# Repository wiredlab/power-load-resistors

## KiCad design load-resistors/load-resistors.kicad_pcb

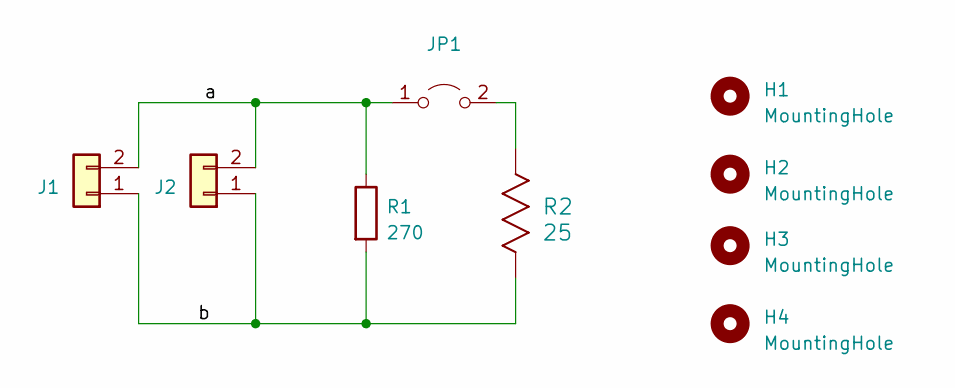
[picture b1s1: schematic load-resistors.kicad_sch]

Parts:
H1, H2, H3, H4: MountingHole; MountingHole_3.2mm_M3
J1, J2: Conn_01x02; Molex_KK-254_AE-6410-02A_1x02_P2.54mm_Vertical
JP1: Jumper_2_Open; PinHeader_1x02_P2.54mm_Vertical
R1: 270; R_Axial_Power_L25.0mm_W9.0mm_P30.48mm
R2: 25; KAL25FB25R0

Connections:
/a: J1.2, J2.2, JP1.1 (A), R1.1
/b: J1.1, J2.1, R1.2, R2.1
unnamed: JP1.2 (B), R2.2

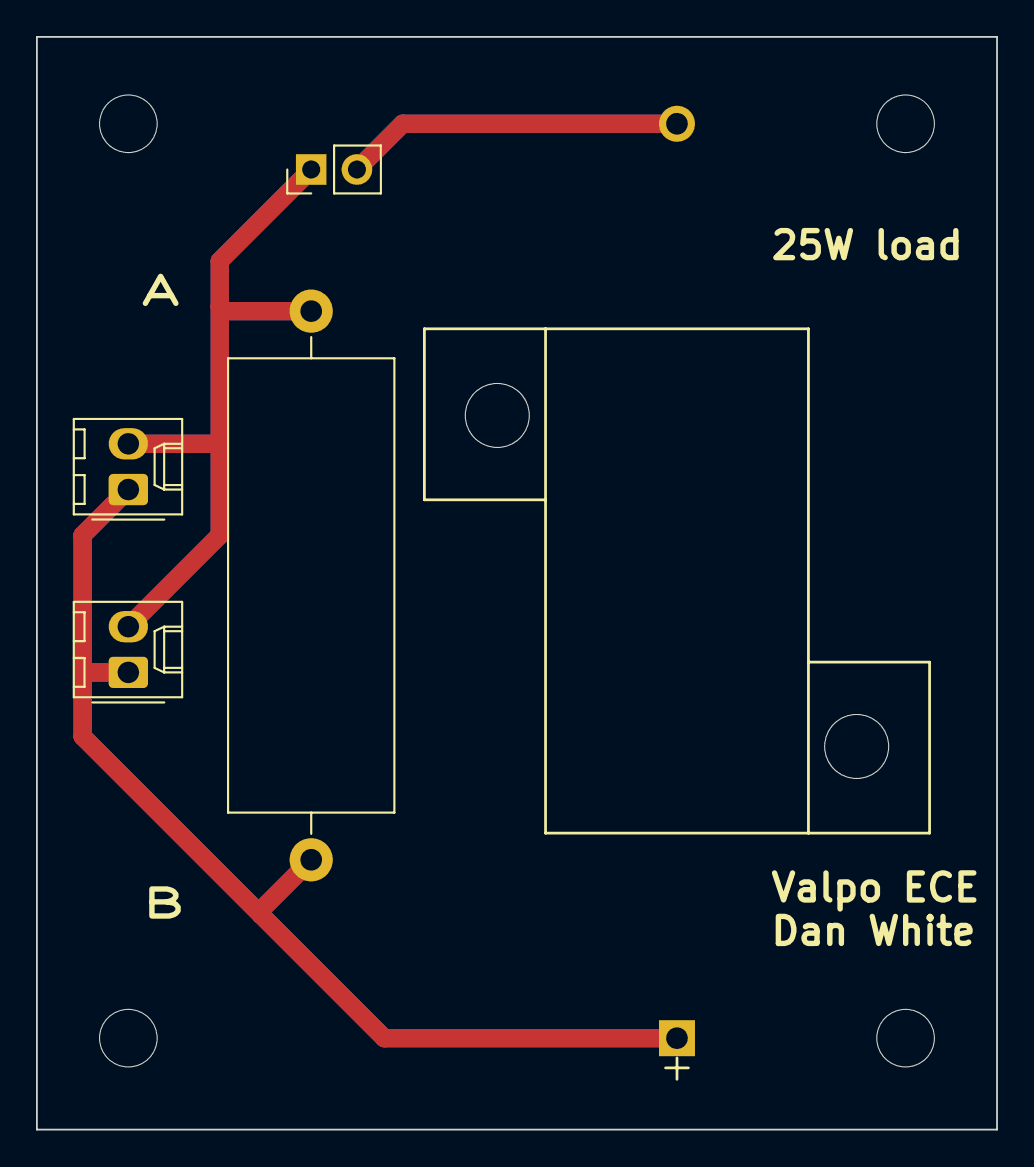
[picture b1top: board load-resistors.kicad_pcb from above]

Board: 2 copper layers, 53.3 x 60.7 mm, 9 parts (0 on the bottom side), 3 nets.

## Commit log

2023-04-18 Ordered version

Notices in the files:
parts and their libraries:
Copyright 2016 Accelerated Designs. All rights reserved.
